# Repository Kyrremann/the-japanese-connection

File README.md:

# The Japanese Connection

With the [Japanese duplex matrix](https://kbd.news/The-Japanese-duplex-matrix-1391.html) you can use less pins for more switches!
So with that in mind we made a hub that let you make split keyboards with no microcontroller, just good old RJ45 and ethernet cables!

## Development

Rember to run `git submodule update` when the [foostan/kbd](https://github.com/foostan/kbd) submodule has been updated.

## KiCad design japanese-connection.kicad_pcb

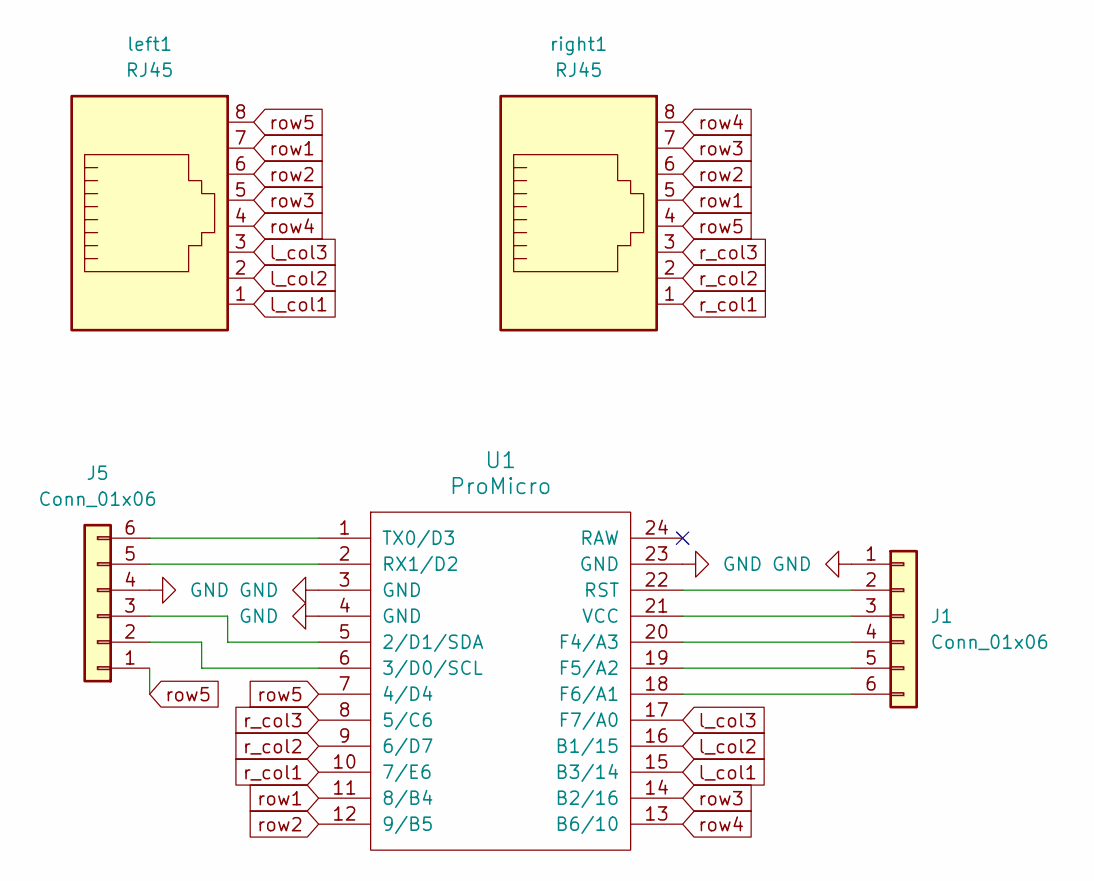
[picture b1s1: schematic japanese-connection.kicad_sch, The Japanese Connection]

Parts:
J1, J5: Conn_01x06; PinSocket_1x06_P2.54mm_Vertical
U1: ProMicro; ProMicro_v3.5
left1: RJ45; RJ45_Amphenol_54602-x08_Horizontal
right1: RJ45; RJ45_Amphenol_54602-x08_Horizontal

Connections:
GND: J1.1, J5.4, U1.3 (GND), U1.4 (GND), U1.23 (GND)
unnamed: J1.2, U1.22 (RST)
unnamed: J1.3, U1.21 (VCC)
unnamed: J1.4, U1.20 (F4/A3)
unnamed: J1.5, U1.19 (F5/A2)
unnamed: J1.6, U1.18 (F6/A1)
unnamed: J5.2, U1.6 (3/D0/SCL)
unnamed: J5.3, U1.5 (2/D1/SDA)
unnamed: J5.5, U1.2 (RX1/D2)
unnamed: J5.6, U1.1 (TX0/D3)
l_col1: U1.15 (B3/14), left1.1
l_col2: U1.16 (B1/15), left1.2
l_col3: U1.17 (F7/A0), left1.3
r_col1: U1.10 (7/E6), right1.1
r_col2: U1.9 (6/D7), right1.2
r_col3: U1.8 (5/C6), right1.3
row1: U1.11 (8/B4), left1.7, right1.5
row2: U1.12 (9/B5), left1.6, right1.6
row3: U1.14 (B2/16), left1.5, right1.7
row4: U1.13 (B6/10), left1.4, right1.8
row5: J5.1, U1.7 (4/D4), left1.8, right1.4

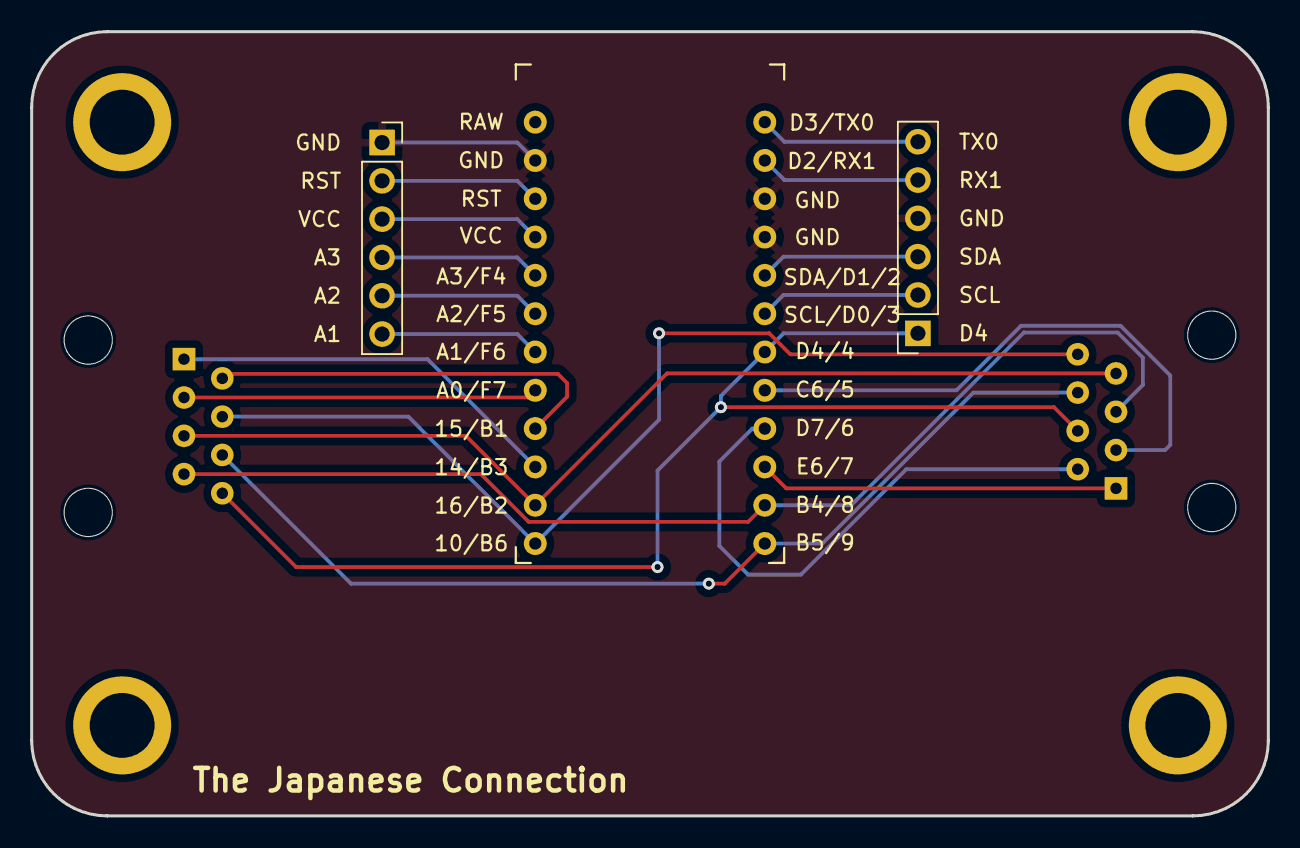
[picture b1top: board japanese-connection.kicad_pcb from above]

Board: 2 copper layers, 82.0 x 52.0 mm, 6 parts (0 on the bottom side), 21 nets.

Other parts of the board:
Ref**: Val**; M2_HOLE

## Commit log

2023-09-27 feat: init commit
2023-09-27 doc: info about submodule
2023-10-08 feat: retraced, matches Cheapino
    It should now be possible to hook a cheapino to this build, with some
    changes to the firmware of course.
